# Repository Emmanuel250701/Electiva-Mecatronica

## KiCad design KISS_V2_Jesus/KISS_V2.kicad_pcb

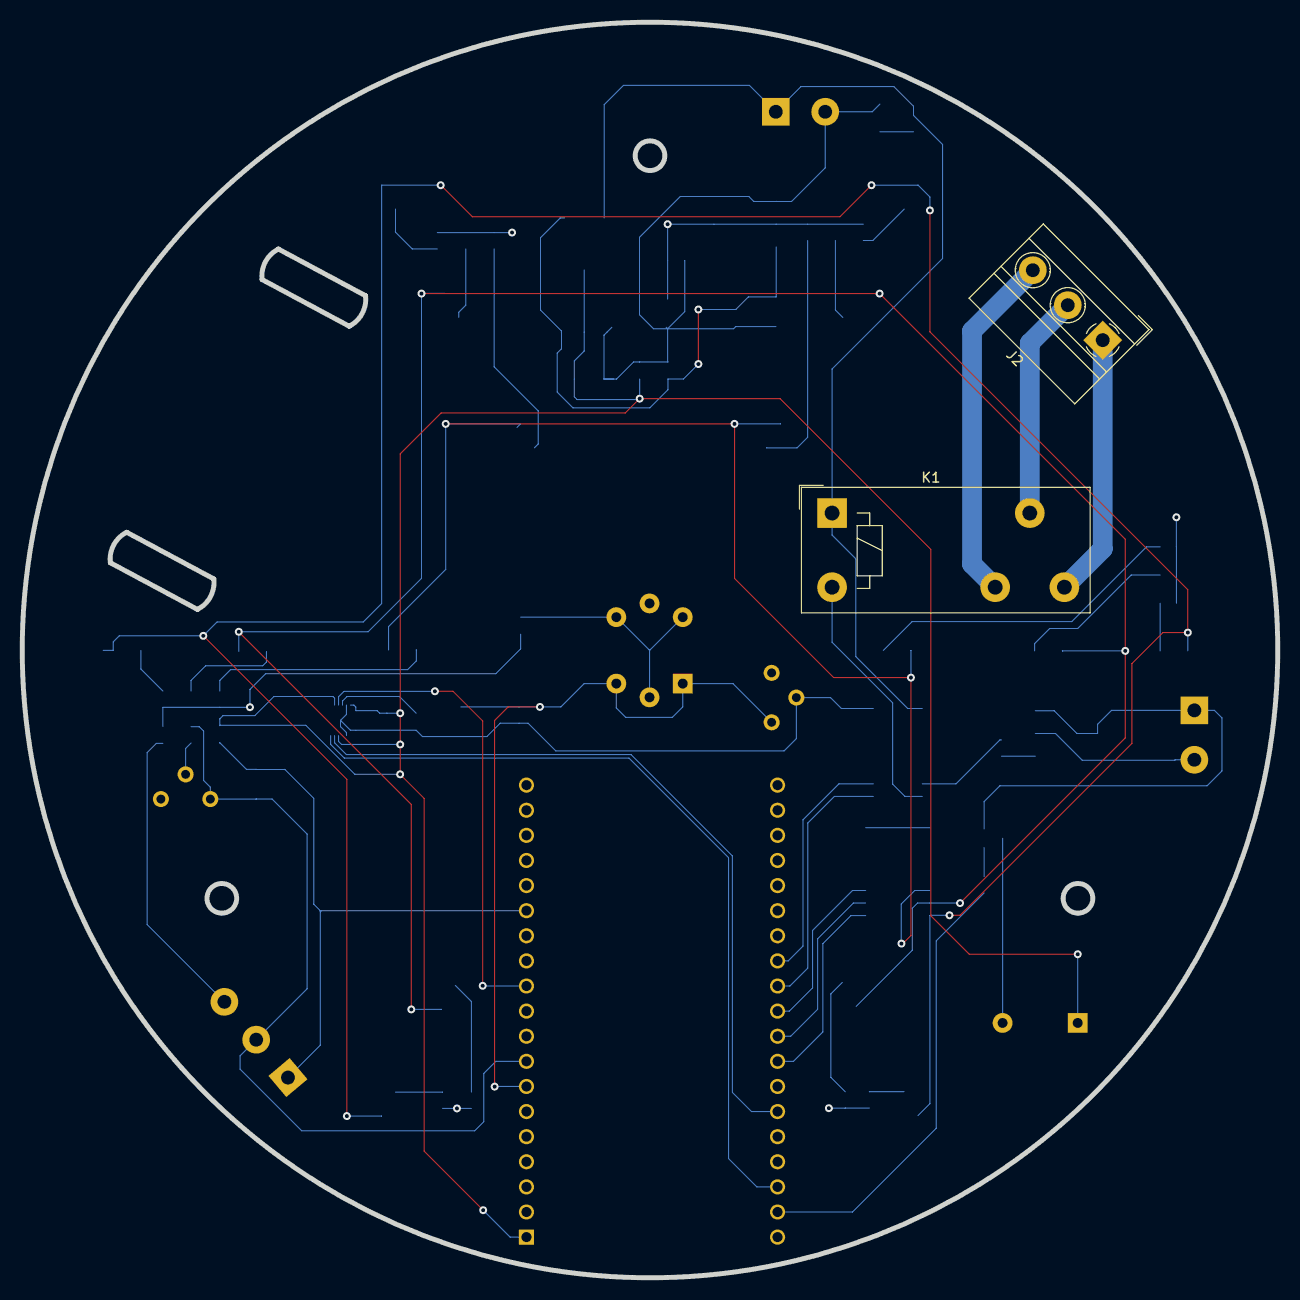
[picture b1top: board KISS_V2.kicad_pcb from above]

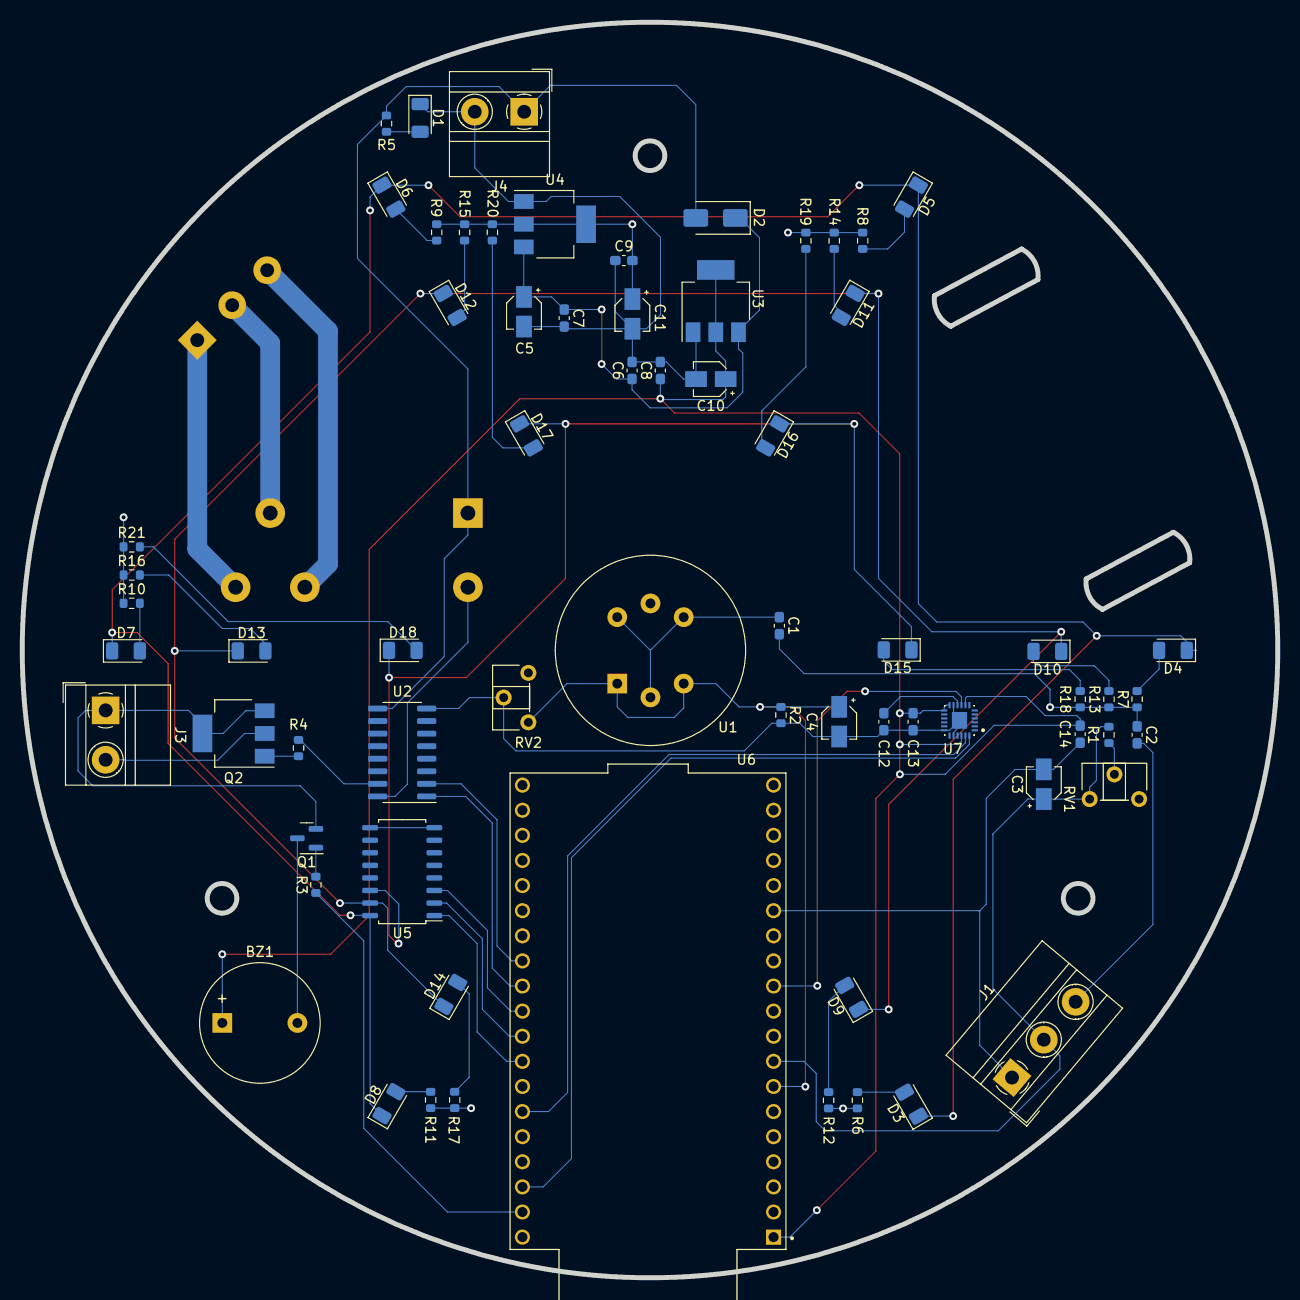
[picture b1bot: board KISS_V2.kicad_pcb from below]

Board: 4 copper layers, 127.0 x 127.0 mm, 70 parts (68 on the bottom side), 49 nets.

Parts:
BZ1: Buzzer; Buzzer_12x9.5RM7.6
C1, C2: 100nF; C_0603_1608Metric_Pad1.08x0.95mm_HandSolder
C3, C4: 4.7 uF; CP_Elec_3x5.3
C5: 100uf; CP_Elec_3x5.3
C6, C7, C8, C9: 100nf; C_0603_1608Metric_Pad1.08x0.95mm_HandSolder
C10, C11: 22uf; CP_Elec_3x5.3
C12, C14: 0.1μF; C_0603_1608Metric_Pad1.08x0.95mm_HandSolder
C13: 10nF; C_0603_1608Metric_Pad1.08x0.95mm_HandSolder
D1, D3, D4, D5, D6, D7, D8, D9, D10, D11, D12, D13, D14, D15, D16, D17, D18: LED; LED_1206_3216Metric
D2: M1; D_SMA
J1, J2: Screw_Terminal_01x03; TerminalBlock_MetzConnect_Type011_RT05503HBWC_1x03_P5.00mm_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
J3, J4: Screw_Terminal_01x02; TerminalBlock_MetzConnect_Type011_RT05502HBWC_1x02_P5.00mm_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
K1: FINDER-40.31; Relay_SPDT_Finder_40.31
Q1: BC817; SOT-23
Q2: BSP75N; SOT-223
R1, R2: 100; R_0603_1608Metric
R3: 1K; R_0603_1608Metric
R4, R5, R6, R7, R8, R9, R10, R11, R12, R13, R14, R15, R16, R17, R18, R19, R20, R21: 220; R_0603_1608Metric
RV1, RV2: 60K; Potentiometer_ACP_CA6-H2,5_Horizontal
U1: MQ-6
U2: ULN2003; SOIC-16_3.9x9.9mm_P1.27mm
U3: AMS1117-3.3; SOT-223-3_TabPin2
U4: AMS1117-5.0; SOT-223-3_TabPin2
U5: ULN2003; SOIC-16_4.55x10.3mm_P1.27mm
U6: ESP32-DEVKITC; MODULE_ESP32-DEVKITC
U7: MPU-6500; QFN40P300X300X95-25N

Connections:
3.3V: BZ1.1 (-), C8.1, C10.1, C13.1, C14.1, U3.2 (VO), U6.1 (3V3), U7.8 (VDDIO), U7.12 (INT), U7.13 (VDD), U7.22 (NCS)
5V: C1.2, C2.1, C9.1, C11.1, R6.1, R7.1, R8.1, R9.1, R10.1, R11.1, R12.1, R13.1, R14.1, R15.1, R16.1, R17.1, R18.1, R19.1, R20.1, R21.1, U4.2 (VO)
/Buzzer/Activador del buzzer: R3.1, U6.37 (IO23)
/Controlador/COM: J2.2, K1.11
/Controlador/Modulo de Diodos/D1: K1.A2, U2.16 (O1)
/Controlador/Modulo de Diodos/EN_D1: U2.1 (I1), U6.28 (IO17)
/Controlador/Modulo de Diodos/EN_D2: U2.2 (I2), U6.27 (IO16)
/Controlador/NA_RL: J2.1, K1.14
/Controlador/NC_RL: J2.3, K1.12
/Controlador/Pin_Activador_LEDam: U5.3 (I3), U6.29 (IO5)
/Controlador/Pin_Activador_LEDaz: U5.2 (I2), U6.30 (IO18)
/Controlador/Pin_Activador_LEDr: U5.1 (I1), U6.31 (IO19)
/Controlador/Pin_Sensor_Gas: C4.1, R2.1, RV2.1, U1.1 (B1), U1.3 (B2), U6.7 (IO32)
/Controlador/Pin_Sensor_GasEx: C3.1, J1.2, R1.1, RV1.1, U6.8 (IO33)
/Controlador/SALIDA TRANSISTOR: J3.2, Q2.2 (D)
/Controlador/SCL: U6.36 (IO22), U7.24 (SDA/SDI)
/Controlador/SDA: U6.33 (IO21), U7.23 (SCL/SCLK)
/Controlador/Salida_Giroscopio: U6.11 (IO27), U7.9 (AD0/SDO)
Activador de transistor: R4.1, U2.15 (O2)
Earth: C3.2, C4.2, C5.2, C6.2, C7.2, C8.2, C9.2, C10.2, C11.2, C12.2, C13.2, C14.2, D1.1 (K), J1.1, J3.1, J4.2, Q1.2 (E), Q2.3 (S), Q2.4 (S), R1.2, R2.2, RV1.2, RV1.3, RV2.2, RV2.3, U1.5 (VH-), U2.8 (GND), U3.1 (GND), U4.1 (GND), U6.14 (GND1), U7.11 (FSYNC), U7.18 (GND), U7.20 (RESV_2), U7.25 (EXP)
GNDREF: U5.8 (GND), U5.9 (COM)
unnamed: BZ1.2 (+), Q1.3 (C)
unnamed: D1.2 (A), R5.2
unnamed: C5.1, C6.1, C7.1, D2.1 (K), U3.3 (VI), U4.3 (VI)
unnamed: D3.2 (A), R6.2
unnamed: D3.1 (K), D4.1 (K), D5.1 (K), D6.1 (K), D7.1 (K), D8.1 (K), U5.16 (O1)
unnamed: D4.2 (A), R7.2
unnamed: D5.2 (A), R8.2
unnamed: D6.2 (A), R9.2
unnamed: D7.2 (A), R10.2
unnamed: D8.2 (A), R11.2
unnamed: D9.2 (A), R12.2
unnamed: D10.2 (A), R13.2
unnamed: D9.1 (K), D10.1 (K), D11.1 (K), D12.1 (K), D13.1 (K), D14.1 (K), U5.15 (O2)
unnamed: D11.2 (A), R14.2
unnamed: D12.2 (A), R15.2
unnamed: D13.2 (A), R16.2
unnamed: D14.2 (A), R17.2
unnamed: D15.2 (A), R18.2
unnamed: D15.1 (K), D16.1 (K), D17.1 (K), D18.1 (K), U5.14 (O3)
unnamed: D16.2 (A), R19.2
unnamed: D17.2 (A), R20.2
unnamed: D18.2 (A), R21.2
unnamed: C2.2, J1.3
unnamed: Q1.1 (B), R3.2
unnamed: Q2.1 (G), R4.2
unnamed: C1.1, U1.2 (VH+), U1.4 (A2), U1.6 (A1)
unnamed: C12.1, U7.10 (REGOUT)
Positivo de bateria: D2.2 (A), J4.1, K1.A1, R5.1, U2.9 (COM)

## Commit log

2023-02-03 Descripcion General
2023-02-03 Requisitos Especificos
2023-02-10 Interfaces
2023-02-10 Interfaz 2
2023-02-17 Manuales
    Manuales de usuario
2023-03-31 Proyecto Kiss
